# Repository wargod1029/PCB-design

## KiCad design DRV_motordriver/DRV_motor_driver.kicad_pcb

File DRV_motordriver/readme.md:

# DRV Motor Driver

Brief
- DRV_motordriver is a brushed motor driver board based on the DRV8701. It provides PWM speed control and enable/disable control for a single motor H-bridge. This README documents usage, test procedures, and maintenance notes — edit the placeholders below with measured/confirmed values.

Key features
- DRV8701-based H-bridge for brushed motors
- PWM speed control (center-zero style: 50% ≈ stop; >50% forward; <50% reverse)
- Enable pin for safe power-up and shutdown

Repository structure
- `DRV_motordriver.kicad_pcb` — PCB layout
- `DRV_motordriver.kicad_sch` — Schematic
- `DRV_motordriver.kicad_pro` — KiCad project file
- `datasheet/` — component datasheets and reference designs
- `lib/` — local symbols & footprints

Electrical overview (fill with measured values)
- Supply voltage (VIN): <e.g. 6–24 V> — confirm actual range
- Recommended motor current limit: <A>
- Fuses / protection: <type/value>

Connectors & pins
- POWER: VIN, GND
- MOTOR: M+, M-
- CONTROL: `PWM` (speed/direction), `EN` (enable), `GND` (signal ground)
- See schematic for exact net names and connector pinouts.

Fabrication notes
- PCB thickness: 1.6 mm (confirm)
- Layer count: 2
- External copper: 1 oz (confirm)
- If you need controlled impedance or internal planes, note that in fabrication files.

BOM
- Use KiCad's BOM export (`bom` plugin) to generate an initial parts list.

KiCad / development notes
- KiCad version used: 8.0
- Local libraries: `lib/DRV8701PRGER` — import instructions are in the `how-to-import.htm` files if needed.

Designer
- Andy, Cheung

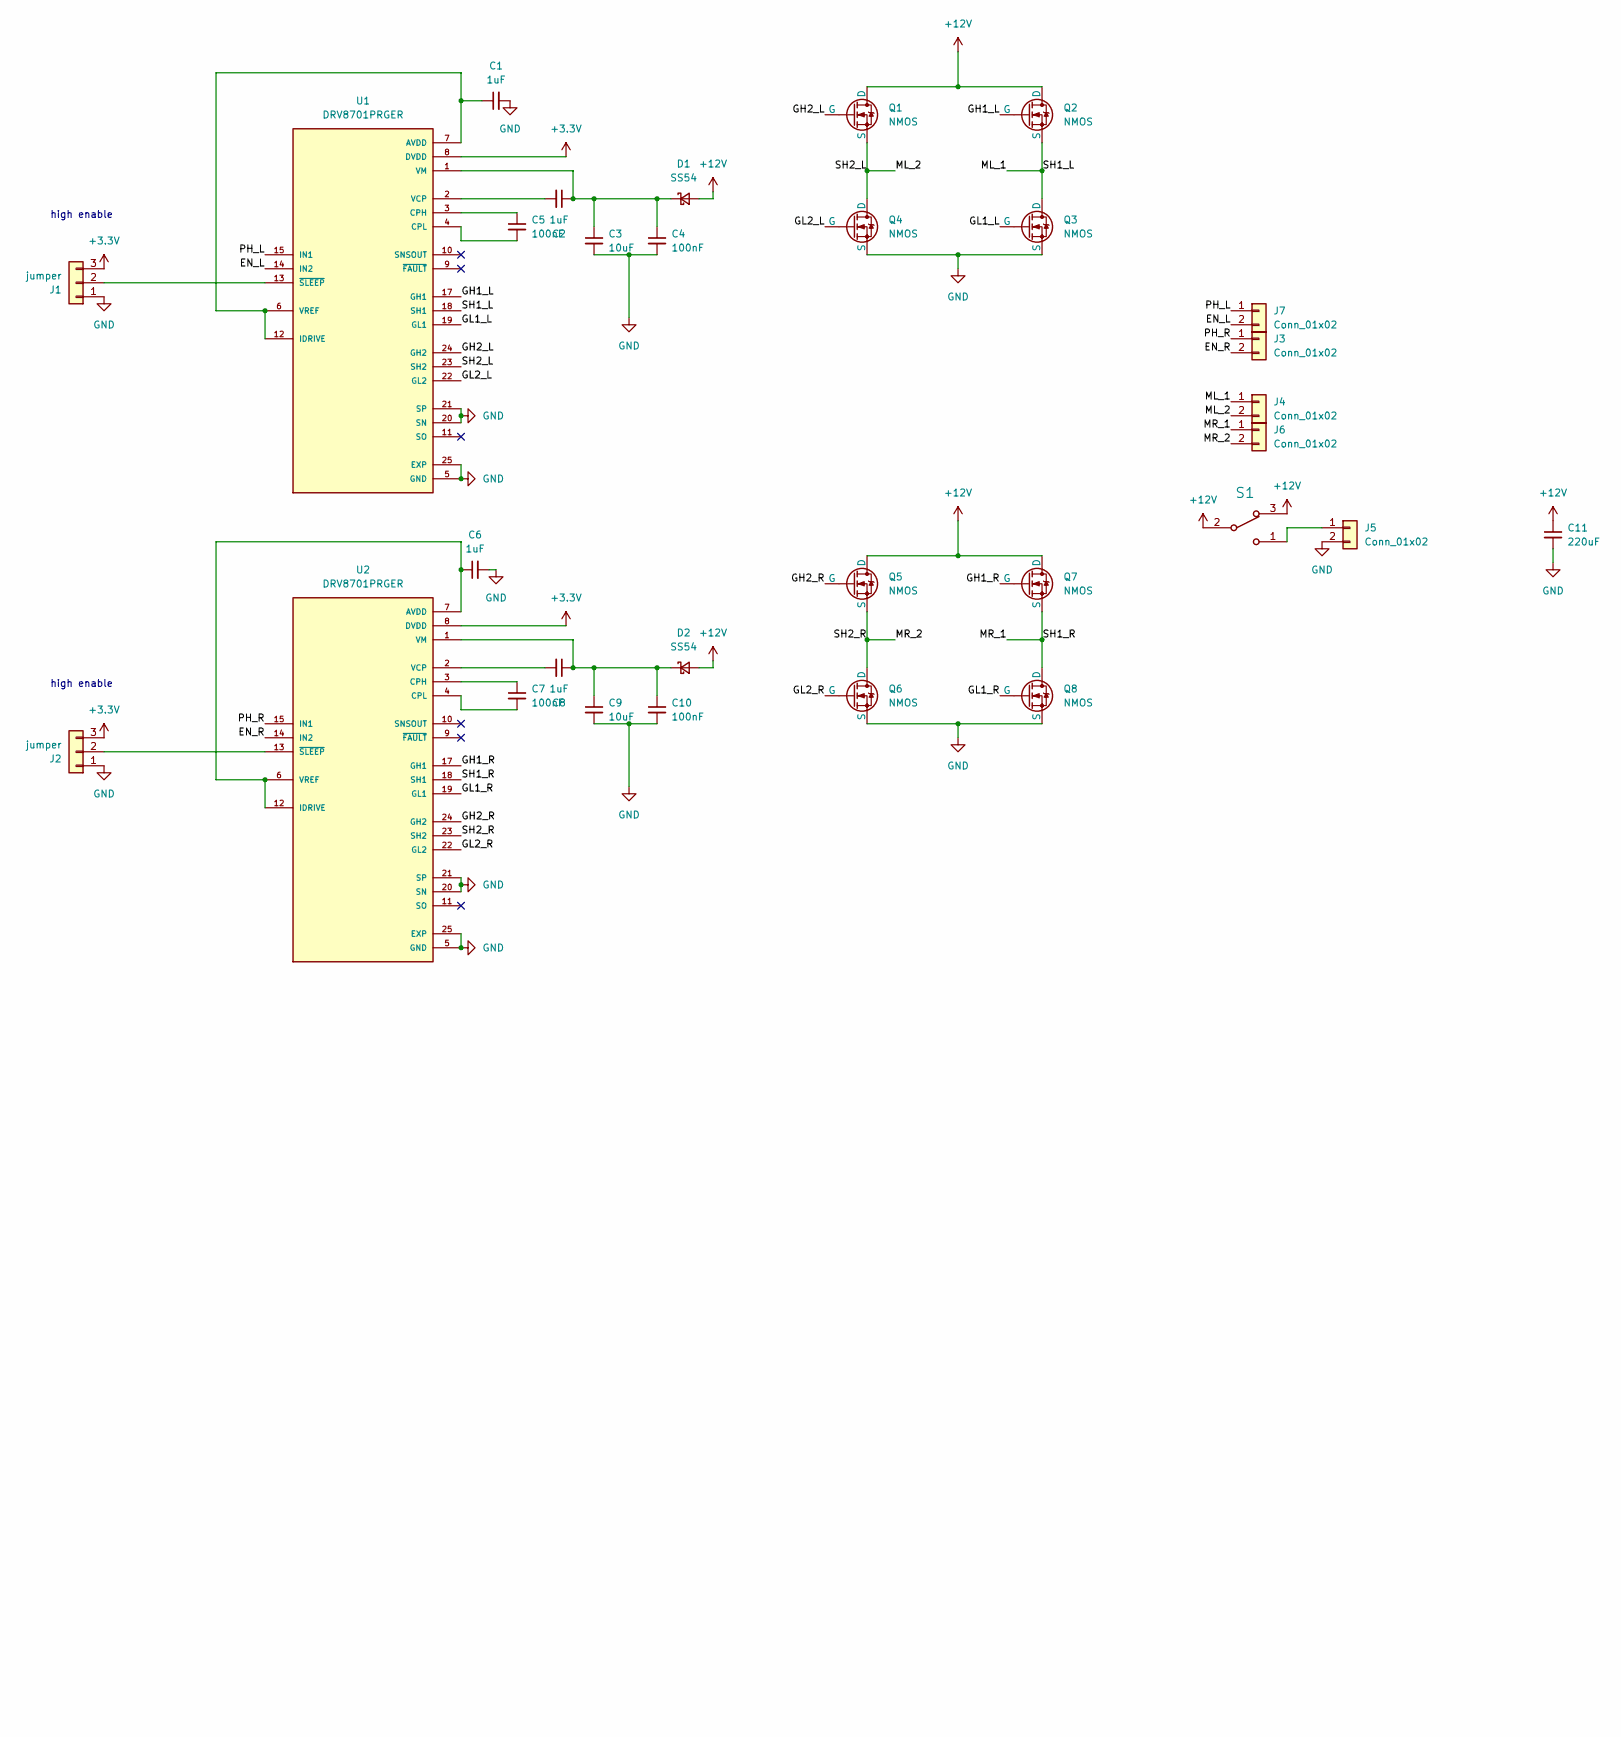
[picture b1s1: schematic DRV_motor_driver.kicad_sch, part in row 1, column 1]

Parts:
C1, C2, C6, C8: 1uF; C_0603_1608Metric
C3, C9: 10uF; C_0603_1608Metric
C4, C5, C7, C10: 100nF; C_0603_1608Metric
C11: 220uF; CP_Radial_D8.0mm_P12.00mm
D1, D2: SS54; D_SMA
H1, H2, H3, H4: MountingHole; MountingHole_3.2mm_M3
J1, J2: jumper; PinHeader_1x03_P2.54mm_Vertical
J3, J7: Conn_01x02; PinHeader_1x02_P2.54mm_Vertical
J4, J6: Conn_01x02; AMASS_XT60-F_1x02_P7.20mm_Vertical
J5: Conn_01x02; AMASS_XT60-M_1x02_P7.20mm_Vertical
Q1, Q2, Q3, Q4, Q5, Q6, Q7, Q8: NMOS; TRANS_TPHR8504PL_L1Q
S1: SW-SPDT; SW_Toggle_Blue_wSlots
U1, U2: DRV8701PRGER; QFN50P400X400X100-25N; PARTREV B

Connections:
+3.3V: J1.3, J2.3, U1.8 (DVDD), U2.8 (DVDD)
+12V: C11.1, D1.2 (A), D2.2 (A), Q1.1 (D), Q2.1 (D), Q5.1 (D), Q7.1 (D), S1.2, S1.3
/EN_L: J7.2, U1.14 (IN2)
/EN_R: J3.2, U2.14 (IN2)
/GH1_L: Q2.2 (G), U1.17 (GH1)
/GH1_R: Q7.2 (G), U2.17 (GH1)
/GH2_L: Q1.2 (G), U1.24 (GH2)
/GH2_R: Q5.2 (G), U2.24 (GH2)
/GL1_L: Q3.2 (G), U1.19 (GL1)
/GL1_R: Q8.2 (G), U2.19 (GL1)
/GL2_L: Q4.2 (G), U1.22 (GL2)
/GL2_R: Q6.2 (G), U2.22 (GL2)
/ML_1: J4.1, Q2.3 (S), Q3.1 (D), U1.18 (SH1)
/ML_2: J4.2, Q1.3 (S), Q4.1 (D), U1.23 (SH2)
/MR_1: J6.1, Q7.3 (S), Q8.1 (D), U2.18 (SH1)
/MR_2: J6.2, Q5.3 (S), Q6.1 (D), U2.23 (SH2)
/PH_L: J7.1, U1.15 (IN1)
/PH_R: J3.1, U2.15 (IN1)
GND: C1.2, C3.2, C4.2, C6.2, C9.2, C10.2, C11.2, J1.1, J2.1, J5.2, Q3.3 (S), Q4.3 (S), Q6.3 (S), Q8.3 (S), U1.5 (GND), U1.16 (GND), U1.20 (SN), U1.21 (SP), U1.25 (EXP), U2.5 (GND), U2.16 (GND), U2.20 (SN), U2.21 (SP), U2.25 (EXP)
unnamed: C2.1, C3.1, C4.1, D1.1 (K), U1.1 (VM)
unnamed: C8.1, C9.1, C10.1, D2.1 (K), U2.1 (VM)
unnamed: J1.2, U1.13 (~SLEEP)
unnamed: J2.2, U2.13 (~SLEEP)
unnamed: J5.1, S1.1
unnamed: C1.1, U1.6 (VREF), U1.7 (AVDD), U1.12 (IDRIVE)
unnamed: C5.1, U1.3 (CPH)
unnamed: C5.2, U1.4 (CPL)
unnamed: C2.2, U1.2 (VCP)
unnamed: C6.1, U2.6 (VREF), U2.7 (AVDD), U2.12 (IDRIVE)
unnamed: C7.1, U2.3 (CPH)
unnamed: C7.2, U2.4 (CPL)
unnamed: C8.2, U2.2 (VCP)

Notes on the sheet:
high enable

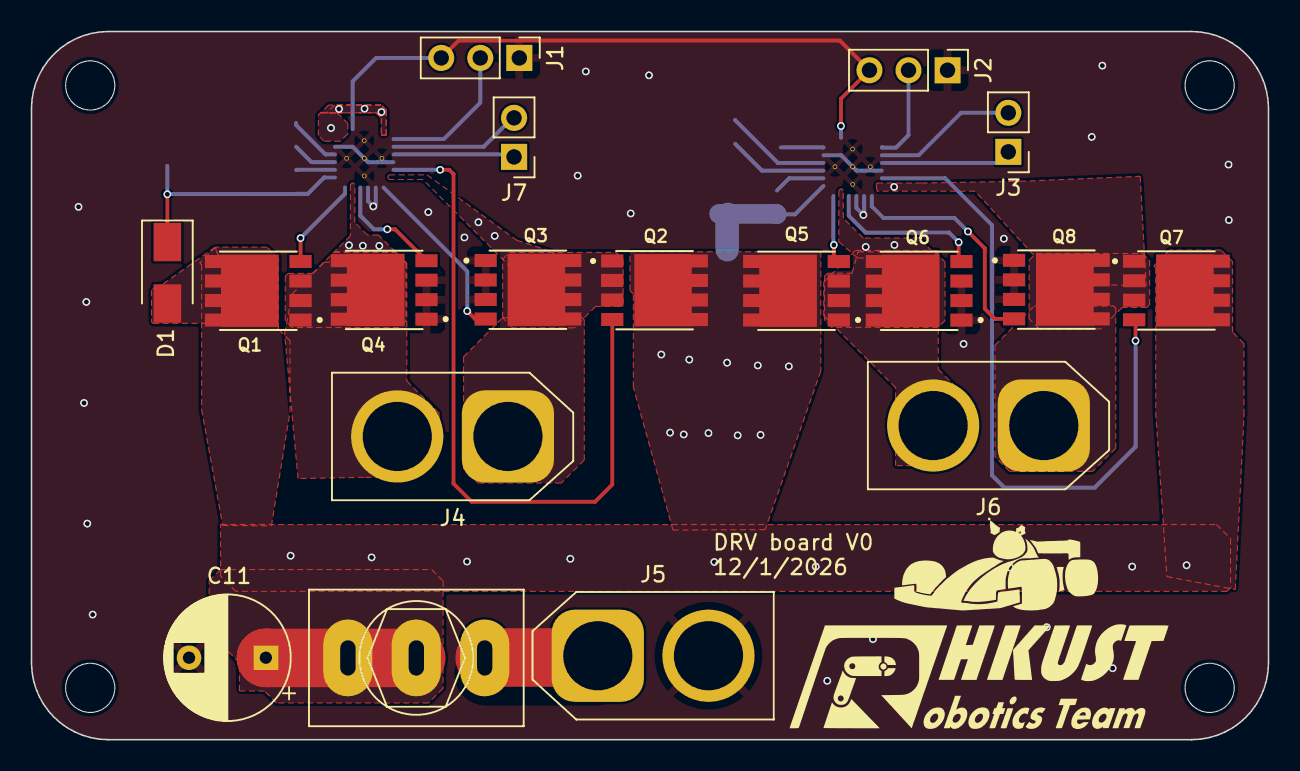
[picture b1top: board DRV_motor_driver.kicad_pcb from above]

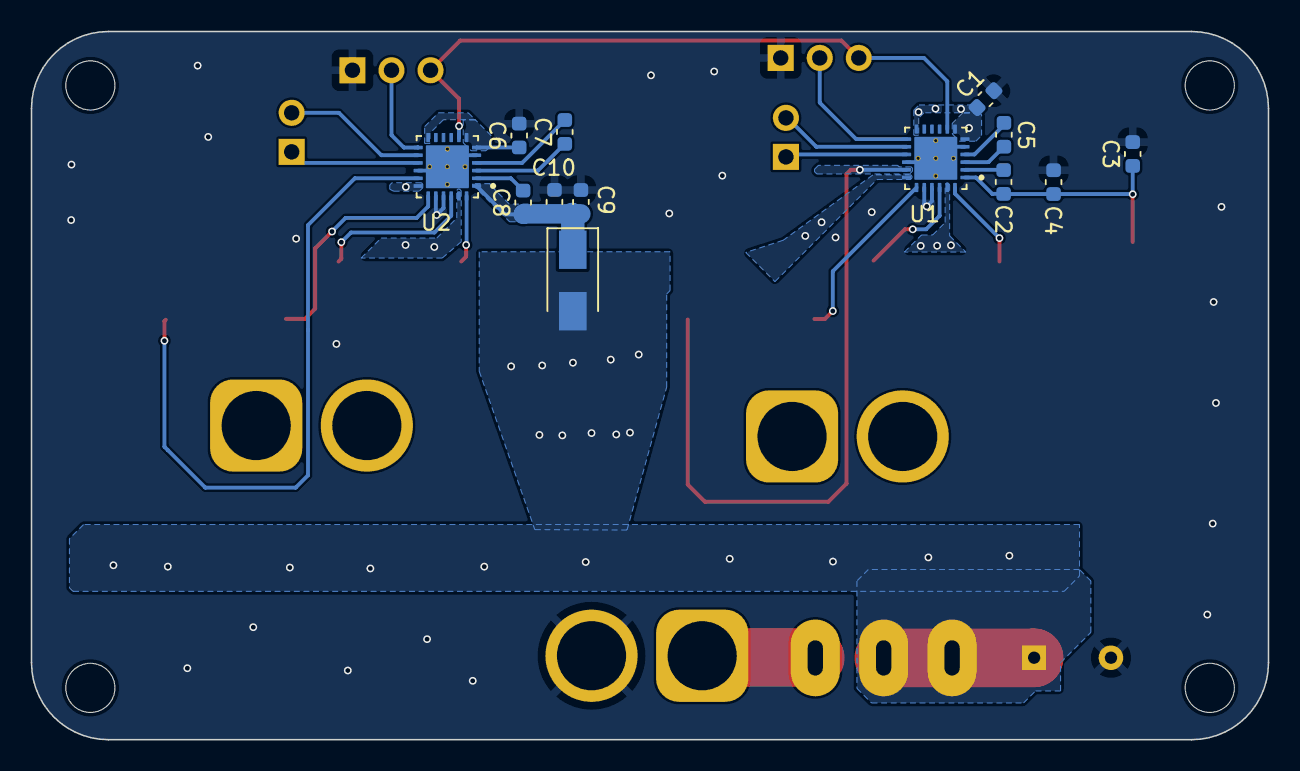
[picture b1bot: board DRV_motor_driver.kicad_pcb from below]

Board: 2 copper layers, 80.5 x 46.1 mm, 35 parts (13 on the bottom side), 32 nets.

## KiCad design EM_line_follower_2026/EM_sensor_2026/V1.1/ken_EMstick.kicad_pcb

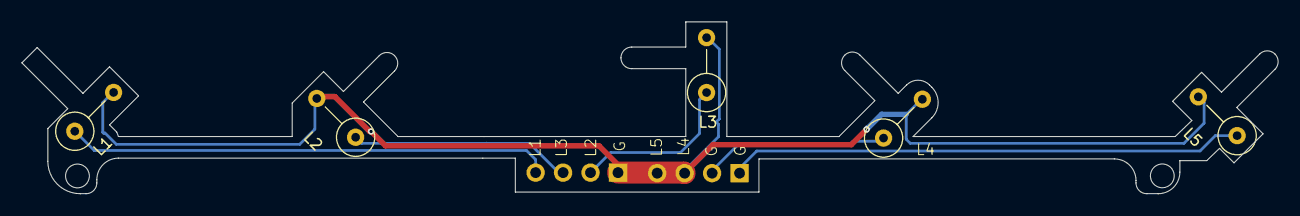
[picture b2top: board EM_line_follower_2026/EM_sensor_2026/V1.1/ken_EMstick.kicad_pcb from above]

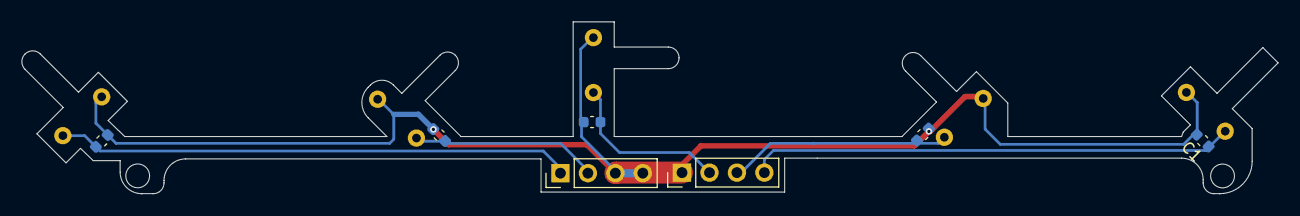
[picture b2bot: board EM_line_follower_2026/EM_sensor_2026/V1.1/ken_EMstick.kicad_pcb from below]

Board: 2 copper layers, 116.3 x 15.9 mm, 14 parts (7 on the bottom side), 6 nets.

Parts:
C1, C2, C3, C4, C5: 6.2nF; C_0603_1608Metric
H1, H2: MountingHole; MountingHole_2.2mm_M2_ISO7380
J3, J4: Conn_01x04; PinHeader_1x04_P2.54mm_Vertical
L1, L2, L3, L4, L5: 10.5mH; L_Axial_L7.0mm_D3.3mm_P5.08mm_Vertical_Fastron_MICC

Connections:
/L1: C1.1, J3.4, L1.1
/L2: C2.1, J3.3, L2.1
/L3: C3.1, J3.2, L3.1
/L4: C4.1, J4.2, L4.1
/L5: C5.1, J4.1, L5.1
GND: C1.2, C2.2, C3.2, C4.2, C5.2, J3.1, J4.3, J4.4, L1.2, L2.2, L3.2, L4.2, L5.2

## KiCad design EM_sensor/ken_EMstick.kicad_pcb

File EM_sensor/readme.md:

# EM_sensor

Brief
- EM sensor board designed to measure magnetic field generated by copper wire with AC signal (20kHz)

Key features
- use LC circuit to detect the AC signal on copper wire in 20kHz and send it to the mainboard by connector

Repository structure
- `ken_EMstick.kicad_pcb` — PCB layout
- `ken_EMstick.kicad_sch` — Schematic
- `ken_EMstick.kicad_pro` — KiCad project file
- `ibom.html` — HTML BOM export

Connectors & pins
- POWER: GND (do not need VCC)
- SENSOR: L1 L2 L3 L4 L5

Fabrication notes
- PCB thickness: 1.6 mm
- Layer count: 2
- Copper thickness: 1 oz external

BOM
- Use KiCad's BOM export (`bom` plugin) to generate an initial parts list.

KiCad / development notes
- KiCad version used: 8.0

Designer
- Andy, Cheung

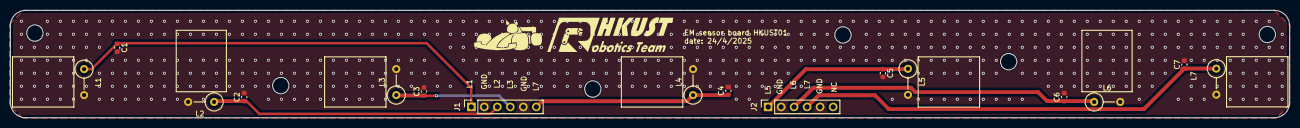
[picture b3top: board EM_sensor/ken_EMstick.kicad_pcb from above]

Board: 2 copper layers, 250.0 x 21.0 mm, 22 parts (0 on the bottom side), 8 nets.

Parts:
C1, C2, C3, C4, C5, C6, C7: 10nF; C_0603_1608Metric
H1, H2, H3, H4, H5, H6: MountingHole; MountingHole_3.2mm_M3
J1, J2: Conn_01x06; PinSocket_1x06_P2.54mm_Vertical
L1, L2, L3, L4, L5, L6, L7: 10.5mH; L_Axial_L7.0mm_D3.3mm_P5.08mm_Vertical_Fastron_MICC

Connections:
/L1: C1.1, J1.1, L1.1
/L2: C2.1, J1.3, L2.1
/L3: C3.1, J1.4, L3.1
/L4: C4.1, J1.6, L4.1
/L5: C5.1, J2.1, L5.1
/L6: C6.1, J2.3, L6.1
/L7: C7.1, J2.4, L7.1
GND: C1.2, C2.2, C3.2, C4.2, C5.2, C6.2, C7.2, J1.2, J1.5, J2.2, J2.5, L1.2, L2.2, L3.2, L4.2, L5.2, L6.2, L7.2

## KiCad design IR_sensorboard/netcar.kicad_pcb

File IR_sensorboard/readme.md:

# IR_sensorboard

Brief
- IR sensor board designed for line-following applications

Key features
- Infrared sensing 

Repository structure
- `netcar.kicad_pcb` — PCB layout
- `netcar.kicad_sch` — Schematic
- `netcar.kicad_pro` — KiCad project file
- `netcar.step` — 3D model export

Electrical overview (fill with measured values)
- Supply voltage: 3.3V - 5V

Connectors & pins
- POWER: VCC, GND
- SENSOR: IR signal outputs by SPI

Fabrication notes
- PCB thickness: 1.6 mm
- Layer count: 2
- Copper thickness: 1 oz external

BOM
- Use KiCad's BOM export (`bom` plugin)

KiCad / development notes
- KiCad version used: 8.0

Designer
- Andy, Cheung

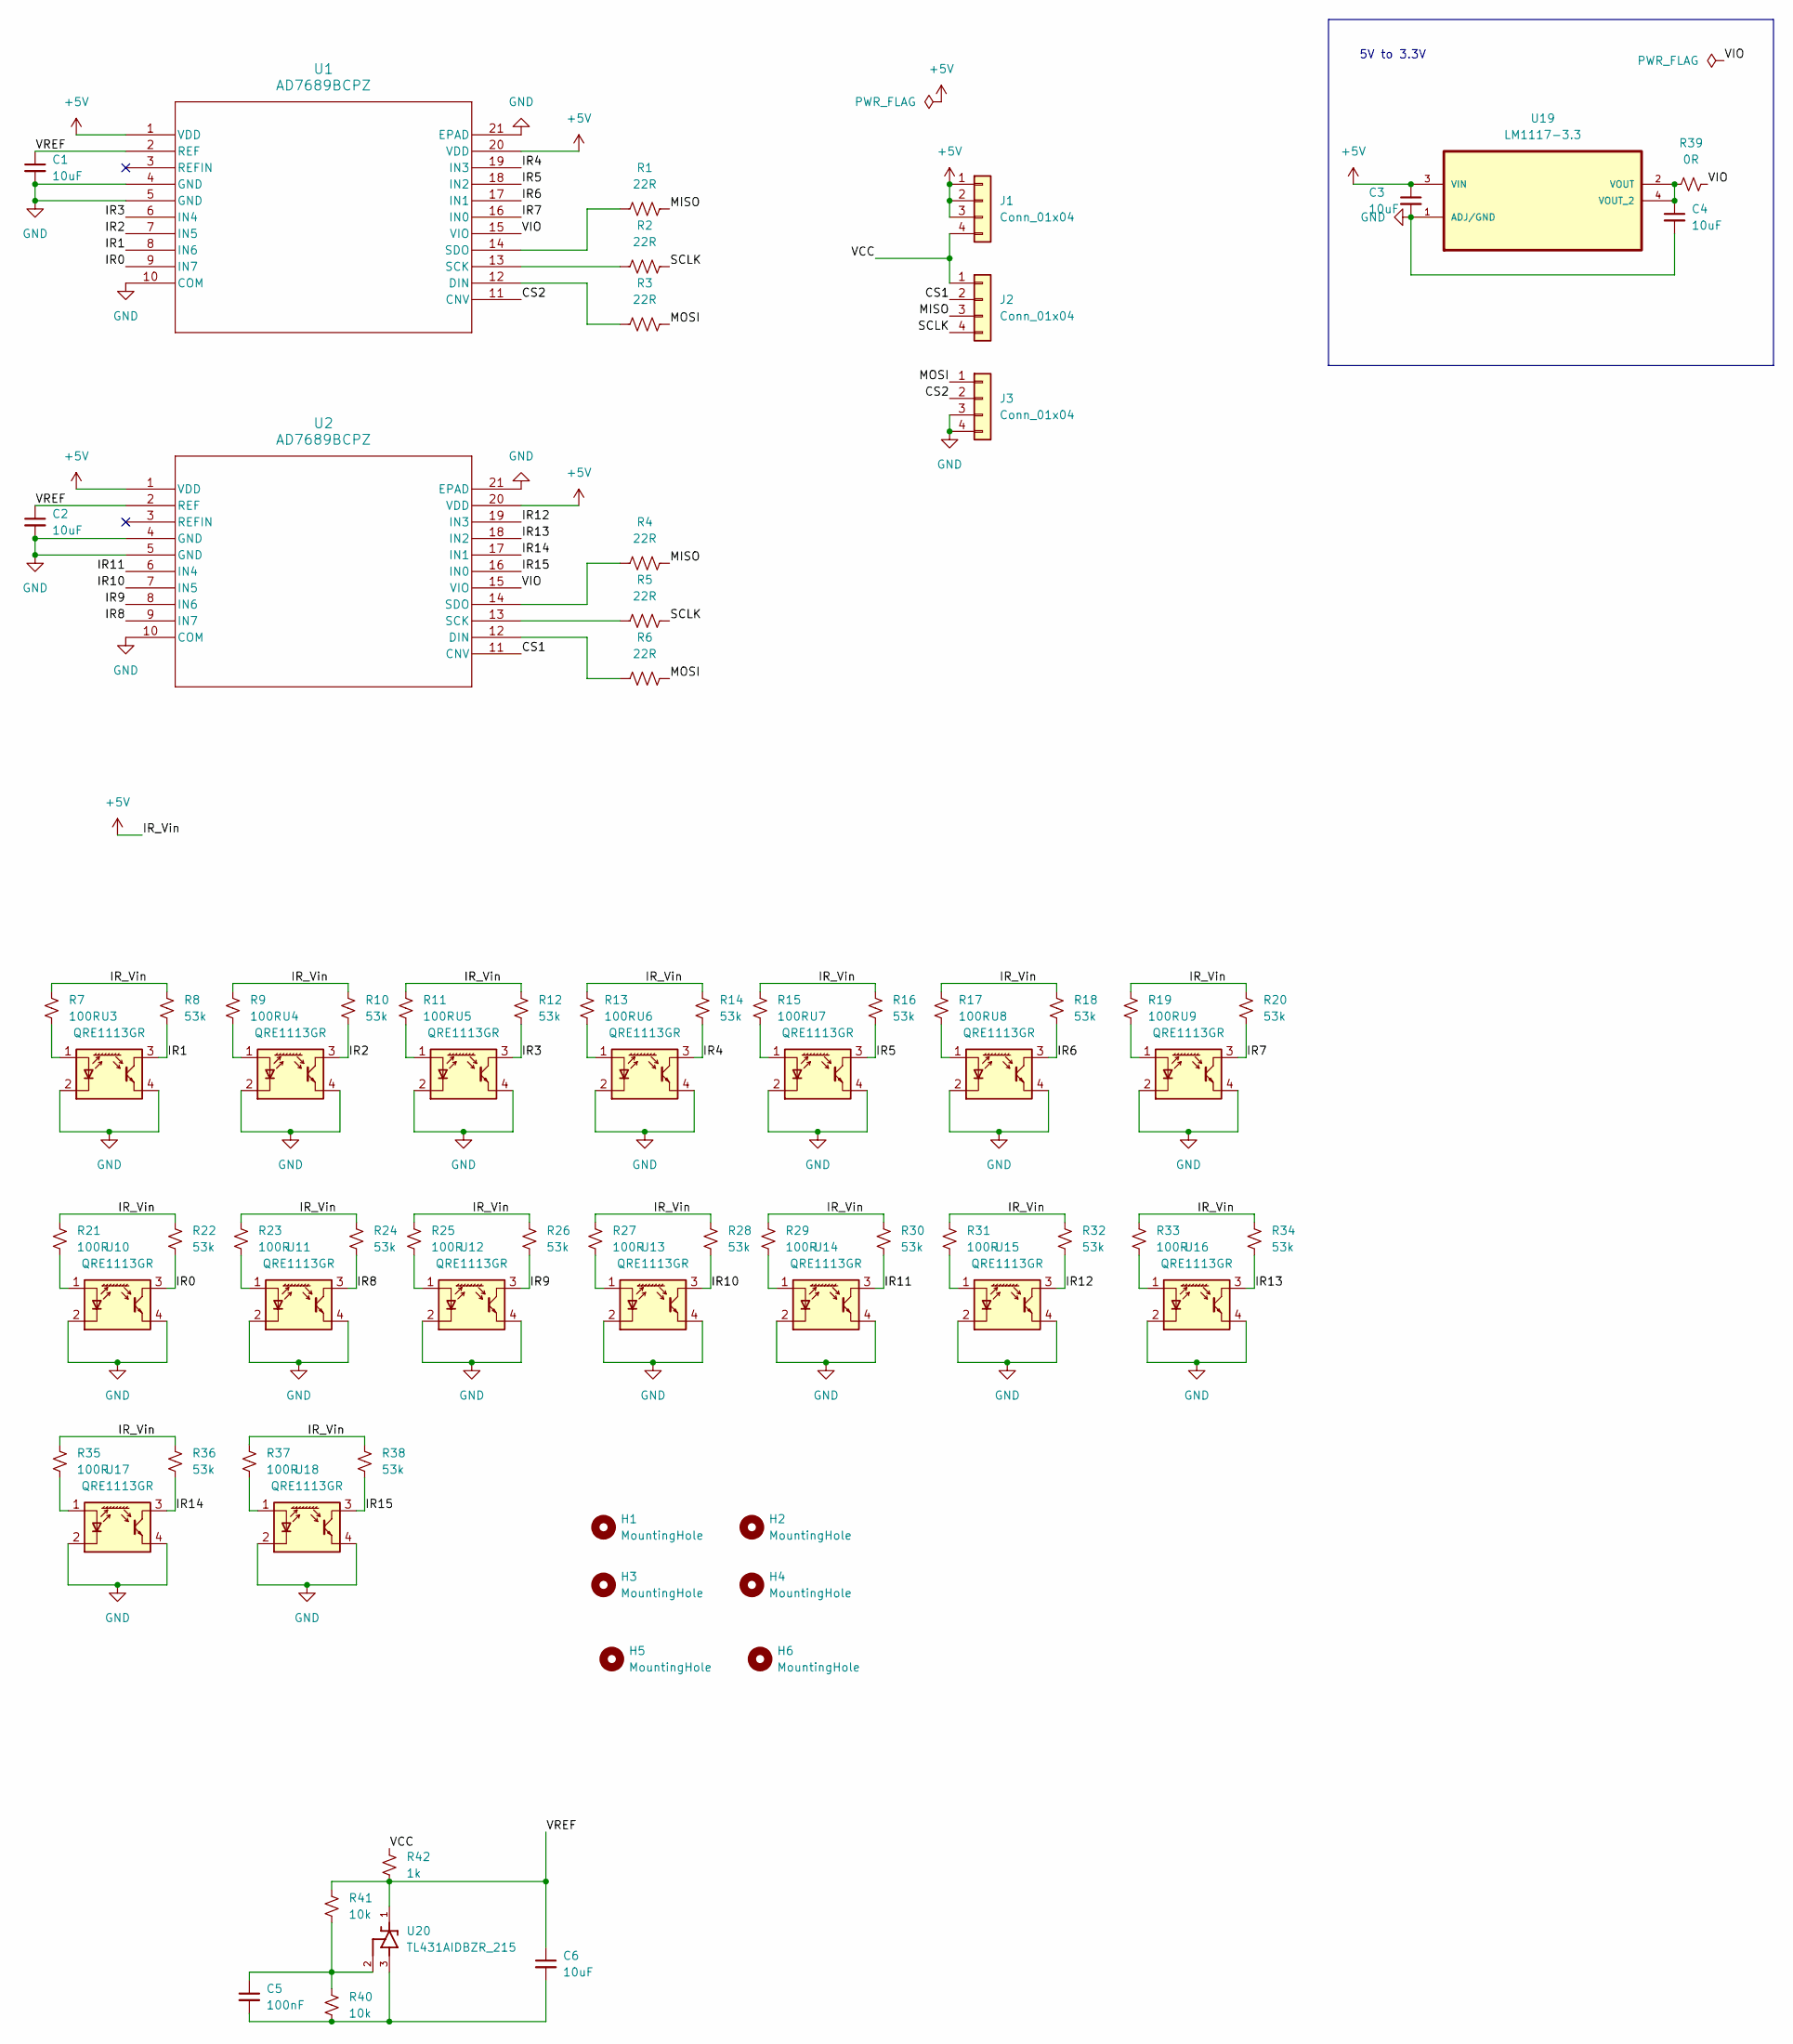
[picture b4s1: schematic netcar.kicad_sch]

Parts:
C1, C2, C3, C4, C6: 10uF; C_0603_1608Metric
C5: 100nF; C_0603_1608Metric
H1, H2, H3, H4, H5, H6: MountingHole; MountingHole_3.2mm_M3
J1, J2, J3: Conn_01x04; JST_XH_S4B-XH-A_1x04_P2.50mm_Horizontal
R1, R2, R3, R4, R5, R6: 22R; R_0603_1608Metric
R7, R9, R11, R13, R15, R17, R19, R21, R23, R25, R27, R29, R31, R33, R35, R37: 100R; R_0603_1608Metric
R8, R10, R12, R14, R16, R18, R20, R22, R24, R26, R28, R30, R32, R34, R36, R38: 53k; R_0603_1608Metric
R39: 0R; R_0603_1608Metric
R40, R41: 10k; R_0603_1608Metric
R42: 1k; R_0603_1608Metric
U1, U2: AD7689BCPZ; CP_20_4_ADI
U3, U4, U5, U6, U7, U8, U9, U10, U11, U12, U13, U14, U15, U16, U17, U18: QRE1113GR; OnSemi_CASE100CY
U19: LM1117-3.3; SOT-223
U20: TL431AIDBZR_215; VREG_TL431AIDBZR_215; PARTREV 6

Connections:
+5V: C3.1, J1.1, J1.2, J1.3, R7.1, R8.1, R9.1, R10.1, R11.1, R12.1, R13.1, R14.1, R15.1, R16.1, R17.1, R18.1, R19.1, R20.1, R21.1, R22.1, R23.1, R24.1, R25.1, R26.1, R27.1, R28.1, R29.1, R30.1, R31.1, R32.1, R33.1, R34.1, R35.1, R36.1, R37.1, R38.1, U1.1 (VDD), U1.20 (VDD), U2.1 (VDD), U2.20 (VDD), U19.3 (VIN)
/CS1: J2.2, U2.11 (CNV)
/CS2: J3.2, U1.11 (CNV)
/IR0: R22.2, U1.9 (IN7), U10.3
/IR1: R8.2, U1.8 (IN6), U3.3
/IR2: R10.2, U1.7 (IN5), U4.3
/IR3: R12.2, U1.6 (IN4), U5.3
/IR4: R14.2, U1.19 (IN3), U6.3
/IR5: R16.2, U1.18 (IN2), U7.3
/IR6: R18.2, U1.17 (IN1), U8.3
/IR7: R20.2, U1.16 (IN0), U9.3
/IR8: R24.2, U2.9 (IN7), U11.3
/IR9: R26.2, U2.8 (IN6), U12.3
/IR10: R28.2, U2.7 (IN5), U13.3
/IR11: R30.2, U2.6 (IN4), U14.3
/IR12: R32.2, U2.19 (IN3), U15.3
/IR13: R34.2, U2.18 (IN2), U16.3
/IR14: R36.2, U2.17 (IN1), U17.3
/IR15: R38.2, U2.16 (IN0), U18.3
/MISO: J2.3, R1.2, R4.2
/MOSI: J3.1, R3.2, R6.2
/SCLK: J2.4, R2.2, R5.2
/VCC: J1.4, J2.1, R42.1
/VIO: R39.1, U1.15 (VIO), U2.15 (VIO)
/VREF: C1.1, C2.1, C6.1, R41.1, R42.2, U1.2 (REF), U2.2 (REF), U20.1
GND: C1.2, C2.2, C3.2, C4.2, J3.3, J3.4, U1.4 (GND), U1.5 (GND), U1.10 (COM), U1.21 (EPAD), U2.4 (GND), U2.5 (GND), U2.10 (COM), U2.21 (EPAD), U3.2 (K), U3.4, U4.2 (K), U4.4, U5.2 (K), U5.4, U6.2 (K), U6.4, U7.2 (K), U7.4, U8.2 (K), U8.4, U9.2 (K), U9.4, U10.2 (K), U10.4, U11.2 (K), U11.4, U12.2 (K), U12.4, U13.2 (K), U13.4, U14.2 (K), U14.4, U15.2 (K), U15.4, U16.2 (K), U16.4, U17.2 (K), U17.4, U18.2 (K), U18.4, U19.1 (ADJ/GND)
unnamed: C5.1, R40.1, R41.2, U20.2
unnamed: C5.2, C6.2, R40.2, U20.3
unnamed: R3.1, U1.12 (DIN)
unnamed: R2.1, U1.13 (SCK)
unnamed: R1.1, U1.14 (SDO)
unnamed: R6.1, U2.12 (DIN)
unnamed: R5.1, U2.13 (SCK)
unnamed: R4.1, U2.14 (SDO)
unnamed: R7.2, U3.1 (A)
unnamed: R9.2, U4.1 (A)
unnamed: R11.2, U5.1 (A)
unnamed: R13.2, U6.1 (A)
unnamed: R15.2, U7.1 (A)
unnamed: R17.2, U8.1 (A)
unnamed: R19.2, U9.1 (A)
unnamed: R21.2, U10.1 (A)
unnamed: R23.2, U11.1 (A)
unnamed: R25.2, U12.1 (A)
unnamed: R27.2, U13.1 (A)
unnamed: R29.2, U14.1 (A)
unnamed: R31.2, U15.1 (A)
unnamed: R33.2, U16.1 (A)
unnamed: R35.2, U17.1 (A)
unnamed: R37.2, U18.1 (A)
unnamed: C4.1, R39.2, U19.2 (VOUT), U19.4 (VOUT_2)

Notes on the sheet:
5V to 3.3V

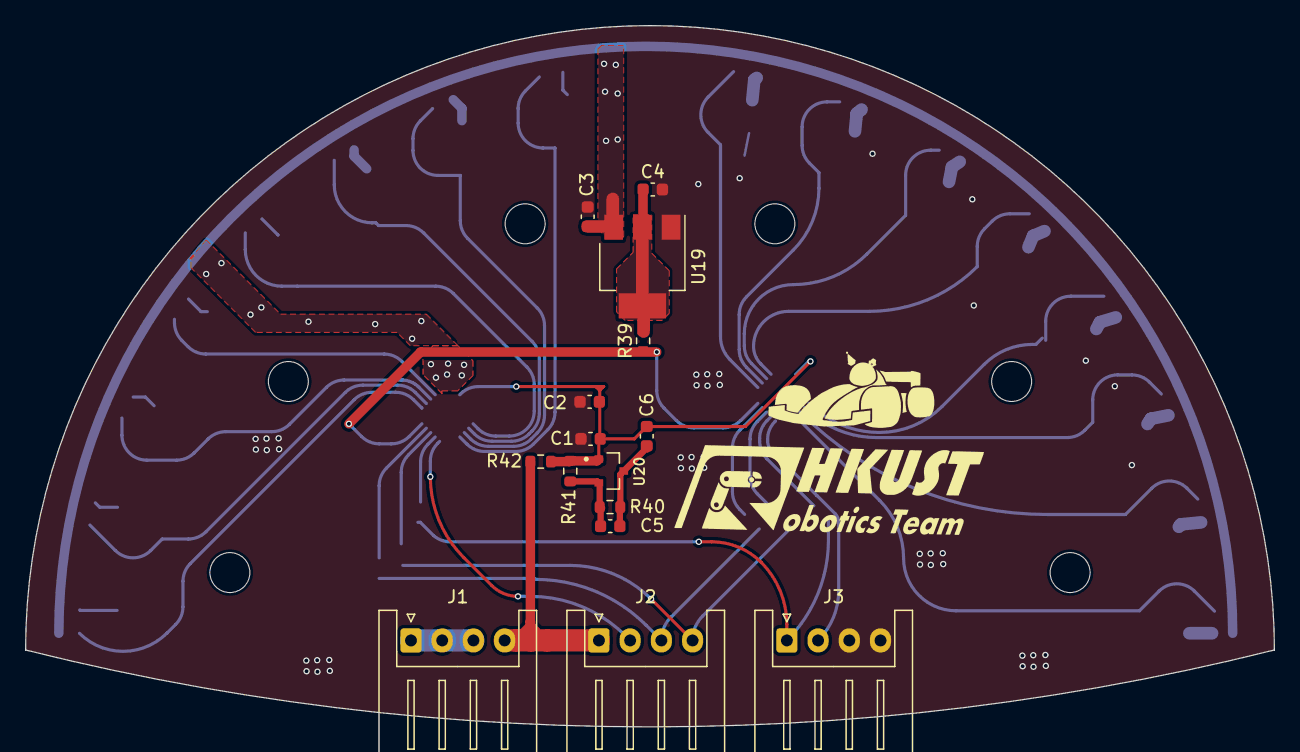
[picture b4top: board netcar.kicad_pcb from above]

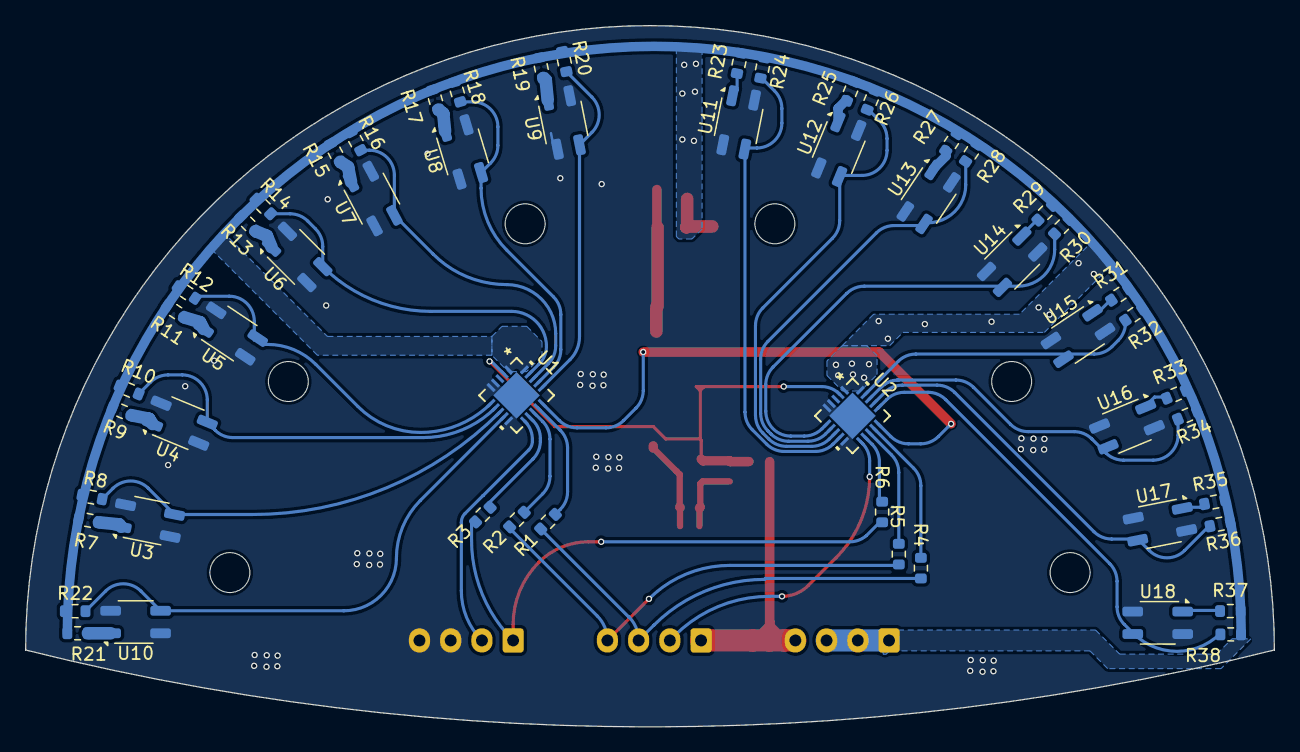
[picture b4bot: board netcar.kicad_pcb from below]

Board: 2 copper layers, 100.0 x 56.2 mm, 77 parts (56 on the bottom side), 51 nets.

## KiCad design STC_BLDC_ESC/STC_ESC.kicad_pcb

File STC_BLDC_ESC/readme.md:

# STC_BLDC_ESC

Brief
- BLDC electronic speed controller board using STC MCU. Intended for aircushion smart car race and drone motor control.

Key features
- BLDC motor driving

Repository structure
- `STC_ESC.kicad_pcb` — PCB layout
- `STC_ESC.kicad_sch` — Schematic
- `STC_ESC.kicad_pro` — KiCad project file
- `lib/` — local symbols and footprints

Electrical overview (fill with measured values)
- Supply voltage: 12V - 24V
- Current rating: <10A>

Connectors & pins
- POWER: VIN, GND
- MOTOR: three phase outputs
- CONTROL: PWM
Fabrication notes
- PCB thickness: 1.6 mm
- Layer count: 2
- Copper thickness: 1 oz external

BOM
- Use KiCad's BOM export (`bom` plugin) 

KiCad / development notes
- KiCad version used: 8.0

Designer
- Jason, CHEN and Andy, Cheung

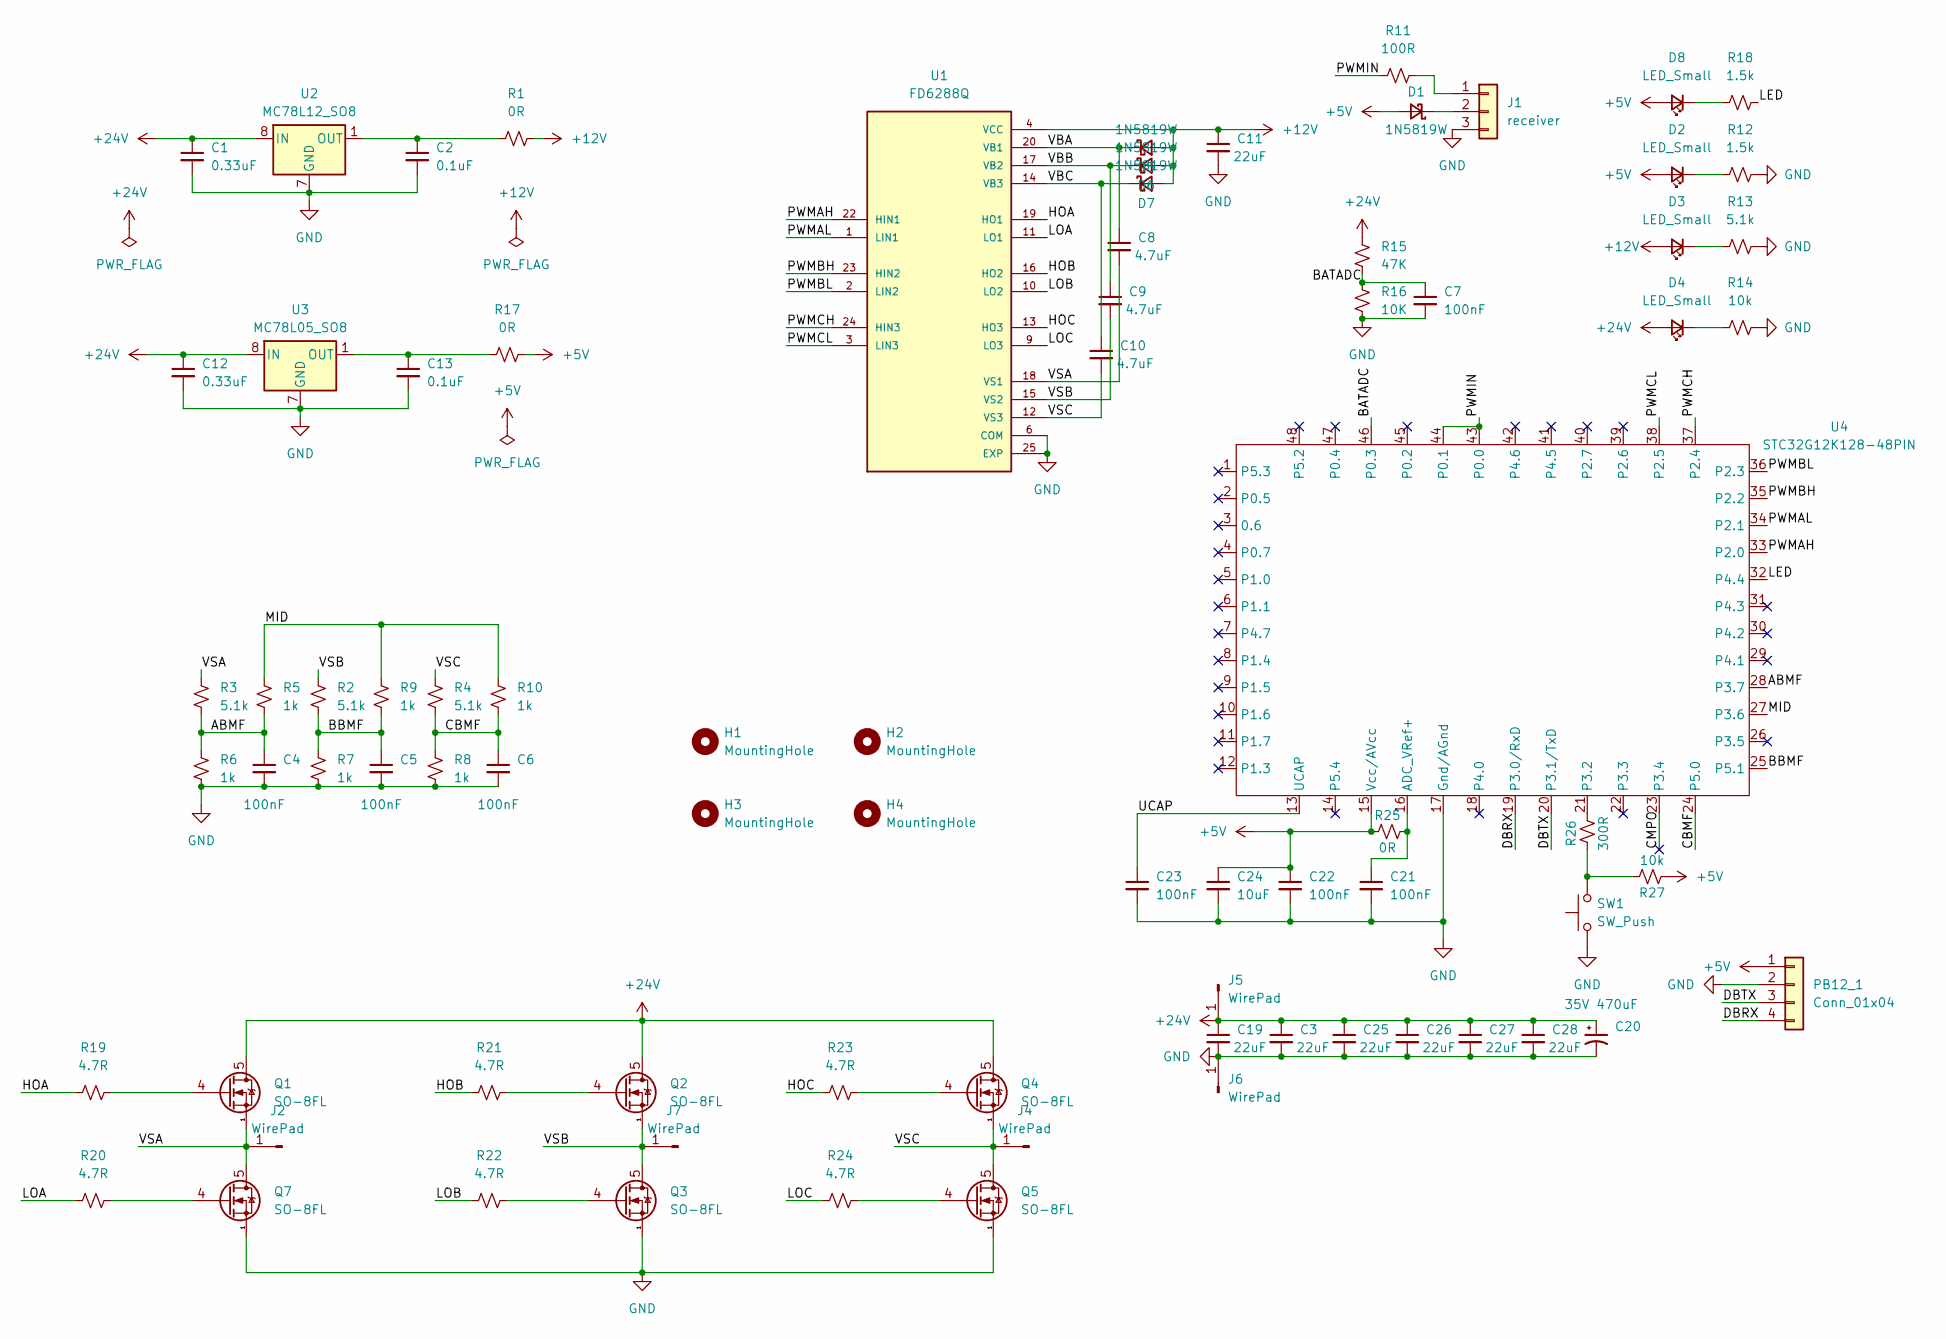
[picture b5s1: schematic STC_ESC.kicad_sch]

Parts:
C1, C12: 0.33uF; C_0603_1608Metric
C2, C13: 0.1uF; C_0603_1608Metric
C3, C19, C25, C26, C27, C28: 22uF; C_1206_3216Metric_Pad1.33x1.80mm_HandSolder
C4, C5, C6, C7, C21, C22, C23: 100nF; C_0603_1608Metric
C8, C9, C10: 4.7uF; C_0603_1608Metric
C11: 22uF; C_0603_1608Metric
C20: 35V 470uF; Big Cap
C24: 10uF; C_0603_1608Metric
D1, D5, D6, D7: 1N5819W; D_SOD-123
D2, D3, D4, D8: LED_Small; LED_0603_1608Metric_Pad1.05x0.95mm_HandSolder
H1, H2, H3, H4: MountingHole; MountingHole_3.2mm_M3
J1: receiver; pad1_3
J2, J4, J5, J6, J7: WirePad
PB12_1: Conn_01x04; JST_XH_B4B-XH-A_1x04_P2.50mm_Vertical
Q1, Q2, Q3, Q4, Q5, Q7: SO−8FL; SO-8FL
R1, R17, R25: 0R; R_0603_1608Metric
R2, R3, R4, R13: 5.1k; R_0603_1608Metric
R5, R6, R7, R8, R9, R10: 1k; R_0603_1608Metric
R11: 100R; R_0603_1608Metric
R12, R18: 1.5k; R_0603_1608Metric
R14, R27: 10k; R_0603_1608Metric
R15: 47K; R_0603_1608Metric
R16: 10K; R_0603_1608Metric
R19, R20, R21, R22, R23, R24: 4.7R; R_0603_1608Metric
R26: 300R; R_0603_1608Metric
SW1: SW_Push
U1: FD6288Q; QFN50P400X400X90-25N
U2: MC78L12_SO8; SOIC-8_3.9x4.9mm_P1.27mm
U3: MC78L05_SO8; SOIC-8_3.9x4.9mm_P1.27mm
U4: STC32G12K128-48PIN; LQFP-48_7x7mm_P0.5mm

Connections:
+5V: C22.1, C24.1, D1.2 (A), D2.2 (A), D8.2 (A), PB12_1.1, R17.2, R25.1, R27.1, U4.15 (Vcc/AVcc)
+12V: C11.1, D3.2 (A), D5.2 (A), D6.2 (A), D7.2 (A), R1.2, U1.4 (VCC)
+24V: C1.1, C3.1, C12.1, C19.1, C20.1, C25.1, C26.1, C27.1, C28.1, D4.2 (A), J5.1, Q1.5 (D), Q2.5 (D), Q4.5 (D), R15.1, U2.8 (IN), U3.8 (IN)
/ABMF: C4.1, R3.2, R5.2, R6.1, U4.28 (P3.7)
/BATADC: C7.1, R15.2, R16.1, U4.46 (P0.3)
/BBMF: C5.1, R2.2, R7.1, R9.2, U4.25 (P5.1)
/CBMF: C6.1, R4.2, R8.1, R10.2, U4.24 (P5.0)
/CMPO: U4.23 (P3.4)
/DBRX: PB12_1.4, U4.19 (P3.0/RxD)
/DBTX: PB12_1.3, U4.20 (P3.1/TxD)
/HOA: R19.1, U1.19 (HO1)
/HOB: R21.1, U1.16 (HO2)
/HOC: R23.1, U1.13 (HO3)
/LED: R18.2, U4.32 (P4.4)
/LOA: R20.1, U1.11 (LO1)
/LOB: R22.1, U1.10 (LO2)
/LOC: R24.1, U1.9 (LO3)
/MID: R5.1, R9.1, R10.1, U4.27 (P3.6)
/PWMAH: U1.22 (HIN1), U4.33 (P2.0)
/PWMAL: U1.1 (LIN1), U4.34 (P2.1)
/PWMBH: U1.23 (HIN2), U4.35 (P2.2)
/PWMBL: U1.2 (LIN2), U4.36 (P2.3)
/PWMCH: U1.24 (HIN3), U4.37 (P2.4)
/PWMCL: U1.3 (LIN3), U4.38 (P2.5)
/PWMIN: R11.1, U4.43 (P0.0), U4.44 (P0.1)
/UCAP: C23.1, U4.13 (UCAP)
/VBA: C8.1, D5.1 (K), U1.20 (VB1)
/VBB: C9.1, D6.1 (K), U1.17 (VB2)
/VBC: C10.1, D7.1 (K), U1.14 (VB3)
/VSA: C8.2, J2.1, Q1.1 (S), Q7.5 (D), R3.1, U1.18 (VS1)
/VSB: C9.2, J7.1, Q2.1 (S), Q3.5 (D), R2.1, U1.15 (VS2)
/VSC: C10.2, J4.1, Q4.1 (S), Q5.5 (D), R4.1, U1.12 (VS3)
GND: C1.2, C2.2, C3.2, C4.2, C5.2, C6.2, C7.2, C11.2, C12.2, C13.2, C19.2, C20.2, C21.2, C22.2, C23.2, C24.2, C25.2, C26.2, C27.2, C28.2, J1.3, J6.1, PB12_1.2, Q3.1 (S), Q5.1 (S), Q7.1 (S), R6.2, R7.2, R8.2, R12.2, R13.2, R14.2, R16.2, SW1.1, U1.6 (COM), U1.25 (EXP), U2.2 (GND), U2.3 (GND), U2.6 (GND), U2.7 (GND), U3.2 (GND), U3.3 (GND), U3.6 (GND), U3.7 (GND), U4.17 (Gnd/AGnd)
unnamed: D1.1 (K), J1.2
unnamed: D2.1 (K), R12.1
unnamed: D3.1 (K), R13.1
unnamed: D4.1 (K), R14.1
unnamed: D8.1 (K), R18.1
unnamed: J1.1, R11.2
unnamed: Q1.4 (G), R19.2
unnamed: Q2.4 (G), R21.2
unnamed: Q3.4 (G), R22.2
unnamed: Q4.4 (G), R23.2
unnamed: Q5.4 (G), R24.2
unnamed: Q7.4 (G), R20.2
unnamed: R26.1, R27.2, SW1.2
unnamed: C2.1, R1.1, U2.1 (OUT)
unnamed: C13.1, R17.1, U3.1 (OUT)
unnamed: C21.1, R25.2, U4.16 (ADC_VRef+)
unnamed: R26.2, U4.21 (P3.2)
